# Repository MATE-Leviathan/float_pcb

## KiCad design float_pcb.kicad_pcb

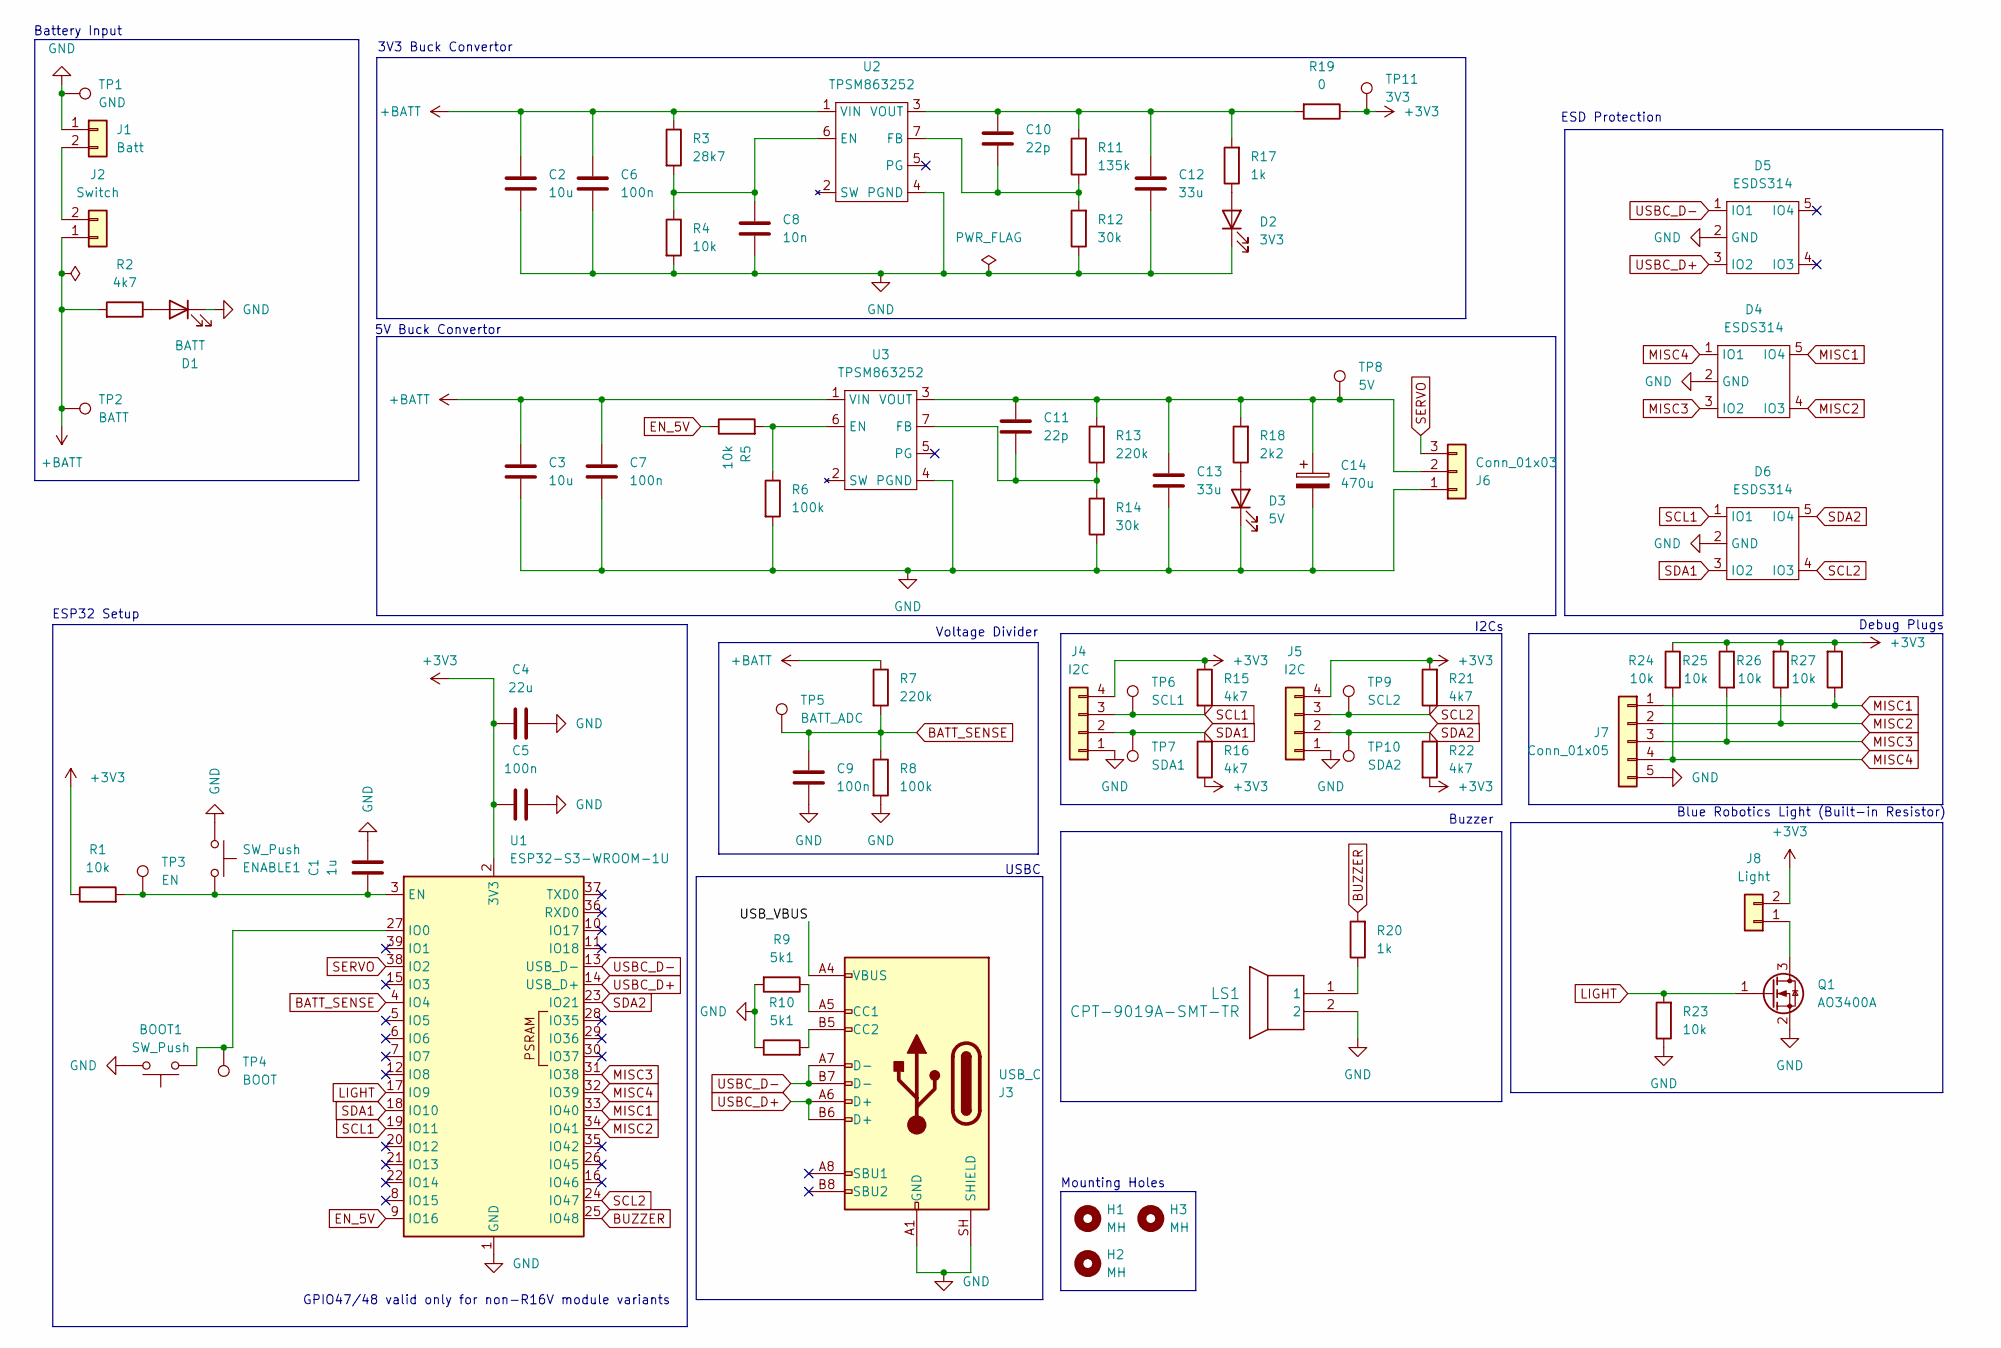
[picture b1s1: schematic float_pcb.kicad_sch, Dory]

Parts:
BOOT1: SW_Push; SW_SPST_TL3342
C1: 1u; C_0603_1608Metric
C2, C3: 10u; C_0805_2012Metric
C4: 22u; C_0603_1608Metric
C5, C6, C7, C9: 100n; C_0603_1608Metric
C8: 10n; C_0603_1608Metric
C10, C11: 22p; C_0603_1608Metric
C12, C13: 33u; C_1206_3216Metric
C14: 470u; CP_Radial_D6.3mm_P2.50mm
D1: BATT; LED_0603_1608Metric
D2: 3V3; LED_0603_1608Metric
D3: 5V; LED_0603_1608Metric
D4, D5, D6: ESDS314; SOT-23-5
ENABLE1: SW_Push; SW_SPST_TL3342
H1, H2, H3: MH; MountingHole_2.2mm_M2
J1: Batt; AMASS_XT30U-M_1x02_P5.0mm_Vertical
J2: Switch; JST_XH_B2B-XH-A_1x02_P2.50mm_Vertical
J3: USB_C; USB_C_Receptacle_GCT_USB4105-xx-A_16P_TopMnt_Horizontal
J4, J5: I2C; JST_XH_B4B-XH-A_1x04_P2.50mm_Vertical
J6: Conn_01x03; JST_XH_B3B-XH-A_1x03_P2.50mm_Vertical
J7: Conn_01x05; PinHeader_1x05_P2.54mm_Vertical
J8: Light; JST_XH_B2B-XH-A_1x02_P2.50mm_Vertical
LS1: CPT-9019A-SMT-TR; CPT-9019A_CUD
Q1: AO3400A; SOT-23
R1, R4, R5, R23, R24, R25, R26, R27: 10k; R_0603_1608Metric
R2, R15, R16, R21, R22: 4k7; R_0603_1608Metric
R3: 28k7; R_0603_1608Metric
R6, R8: 100k; R_0603_1608Metric
R7, R13: 220k; R_0603_1608Metric
R9, R10: 5k1; R_0603_1608Metric
R11: 135k; R_0603_1608Metric
R12, R14: 30k; R_0603_1608Metric
R17, R20: 1k; R_0603_1608Metric
R18: 2k2; R_0603_1608Metric
R19: 0; R_0603_1608Metric
TP1: GND; TestPoint_Pad_D1.5mm
TP2: BATT; TestPoint_Pad_D1.5mm
TP3: EN; TestPoint_Pad_D1.5mm
TP4: BOOT; TestPoint_Pad_D1.5mm
TP5: BATT_ADC; TestPoint_Pad_D1.5mm
TP6: SCL1; TestPoint_Pad_D1.5mm
TP7: SDA1; TestPoint_Pad_D1.5mm
TP8: 5V; TestPoint_Pad_D1.5mm
TP9: SCL2; TestPoint_Pad_D1.5mm
TP10: SDA2; TestPoint_Pad_D1.5mm
TP11: 3V3; TestPoint_Pad_D1.5mm
U1: ESP32-S3-WROOM-1U
U2, U3: TPSM863252; TPSM86325x_RDX0007A

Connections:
+3V3: C4.1, C5.1, J4.4, J5.4, J8.2, R1.1, R15.1, R16.1, R19.1, R21.2, R22.2, R24.1, R25.1, R26.2, R27.2, TP11.1 (1_1), U1.2 (3V3)
+BATT: C2.1, C3.1, C6.2, C7.2, J2.1, R2.2, R3.1, R7.1, TP2.1 (1_1), U2.1 (VIN), U3.1 (VIN)
/USB_VBUS: J3.A4 (VBUS), J3.A9 (VBUS), J3.B4 (VBUS), J3.B9 (VBUS)
BATT_SENSE: C9.1, R7.2, R8.1, TP5.1 (1_1), U1.4 (IO4)
BUZZER: R20.2, U1.25 (IO48)
EN_5V: R5.1, U1.9 (IO16)
GND: BOOT1.2, C1.1, C2.2, C3.2, C4.2, C5.2, C6.1, C7.1, C8.1, C9.2, C12.1, C13.1, C14.2, D1.1 (K), D2.1 (K), D3.1 (K), D4.2 (GND), D5.2 (GND), D6.2 (GND), ENABLE1.1, J1.1, J3.A1 (GND), J3.A12 (GND), J3.B1 (GND), J3.B12 (GND), J3.SH (SHIELD), J4.1, J5.1, J6.1, J7.5, LS1.2, Q1.2 (S), R4.2, R6.2, R8.2, R9.2, R10.1, R12.1, R14.1, R23.1, TP1.1 (1_1), U1.1 (GND), U1.40 (GND), U1.41 (GND), U2.4 (PGND), U3.4 (PGND)
LIGHT: Q1.1 (G), R23.2, U1.17 (IO9)
MISC1: D4.5 (IO4), J7.1, R27.1, U1.33 (IO40)
MISC2: D4.4 (IO3), J7.2, R26.1, U1.34 (IO41)
MISC3: D4.3 (IO2), J7.3, R25.2, U1.31 (IO38)
MISC4: D4.1 (IO1), J7.4, R24.2, U1.32 (IO39)
unnamed: D1.2 (A), R2.1
unnamed: D2.2 (A), R17.1
unnamed: D3.2 (A), R18.1
unnamed: J1.2, J2.2
unnamed: J3.A5 (CC1), R9.1
unnamed: J3.B5 (CC2), R10.2
unnamed: C11.1, C13.2, C14.1, J6.2, R13.2, R18.2, TP8.1 (1_1), U3.3 (VOUT)
unnamed: J8.1, Q1.3 (D)
unnamed: LS1.1, R20.1
unnamed: C1.2, ENABLE1.2, R1.2, TP3.1 (1_1), U1.3 (EN)
unnamed: BOOT1.1, TP4.1 (1_1), U1.27 (IO0)
unnamed: C8.2, R3.2, R4.1, U2.6 (EN)
unnamed: C10.2, R11.1, R12.2, U2.7 (FB)
unnamed: C10.1, C12.2, R11.2, R17.2, R19.2, U2.3 (VOUT)
unnamed: R5.2, R6.1, U3.6 (EN)
unnamed: C11.2, R13.1, R14.2, U3.7 (FB)
SCL1: D6.1 (IO1), J4.3, R15.2, TP6.1 (1_1), U1.19 (IO11)
SCL2: D6.4 (IO3), J5.3, R21.1, TP9.1 (1_1), U1.24 (IO47)
SDA1: D6.3 (IO2), J4.2, R16.2, TP7.1 (1_1), U1.18 (IO10)
SDA2: D6.5 (IO4), J5.2, R22.1, TP10.1 (1_1), U1.23 (IO21)
SERVO: J6.3, U1.38 (IO2)
USBC_D+: D5.3 (IO2), J3.A6 (D+), J3.B6 (D+), U1.14 (USB_D+)
USBC_D-: D5.1 (IO1), J3.A7 (D-), J3.B7 (D-), U1.13 (USB_D-)

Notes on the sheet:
Mounting Holes
ESP32 Setup
I2Cs
ESD Protection
Battery Input
USBC
3V3 Buck Convertor
Blue Robotics Light (Built-in Resistor)
5V Buck Convertor
GPIO47/48 valid only for non-R16V module variants
Buzzer
Voltage Divider
Debug Plugs

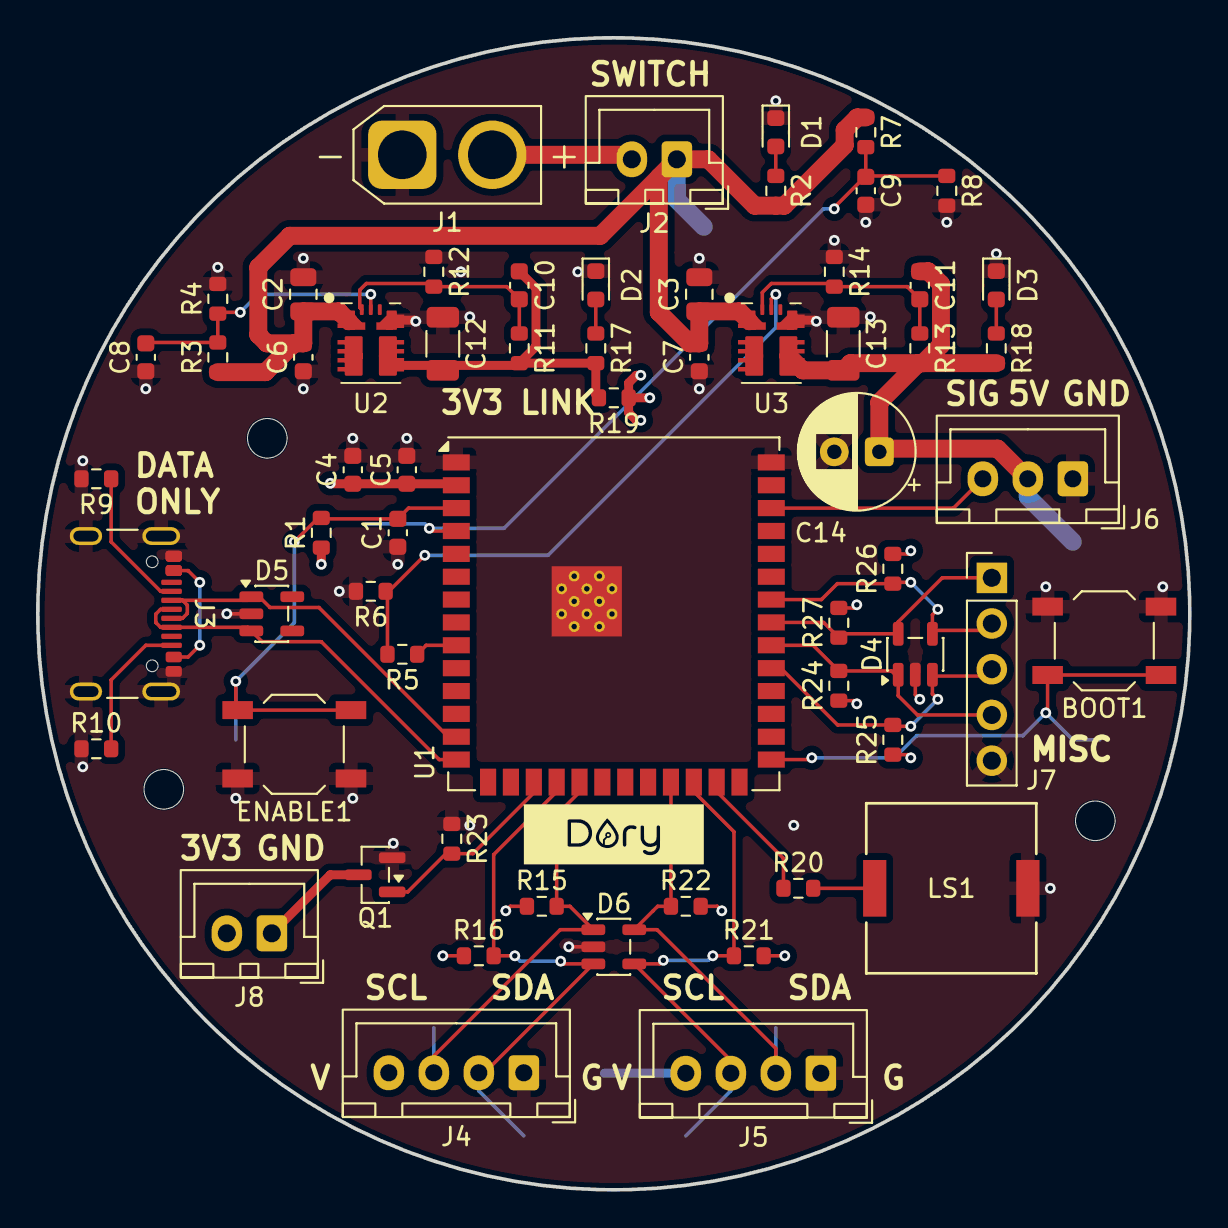
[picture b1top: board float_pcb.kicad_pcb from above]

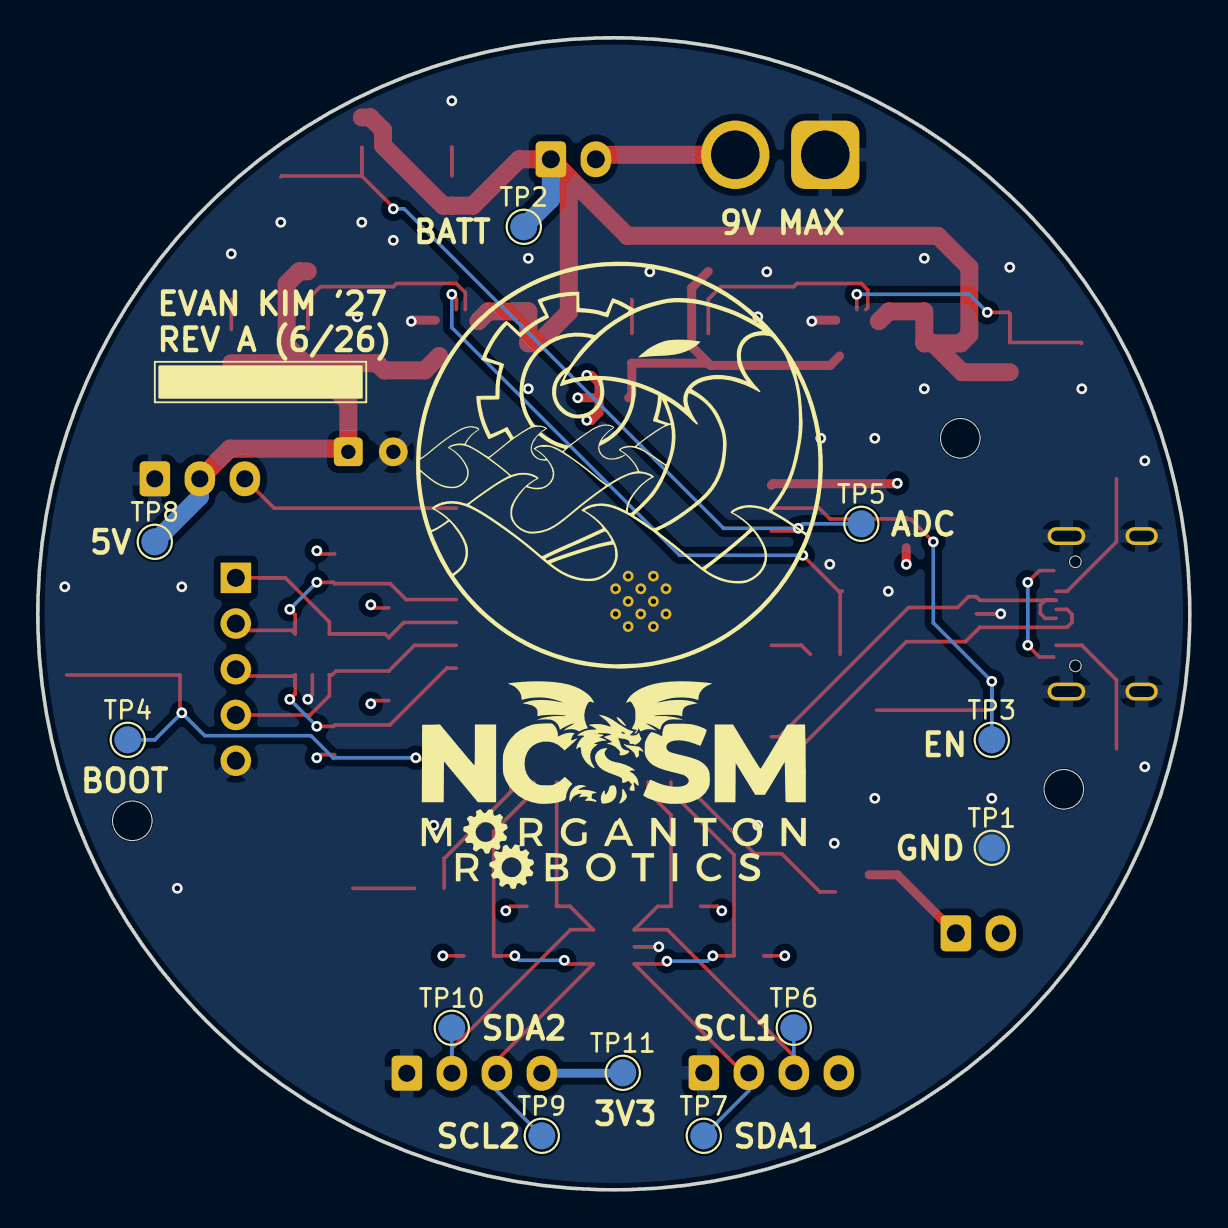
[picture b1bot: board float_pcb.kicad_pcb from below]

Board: 4 copper layers, 64.0 x 64.0 mm, 76 parts (11 on the bottom side), 35 nets.

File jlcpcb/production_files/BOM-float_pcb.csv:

Comment,Designator,Footprint,LCSC,Quantity
Conn_01x03,J6,JST_XH_B3B-XH-A_1x03_P2.50mm_Vertical,,1
Batt,J1,AMASS_XT30U-M_1x02_P5.0mm_Vertical,,1
470u,C14,CP_Radial_D6.3mm_P2.50mm,,1
100n,C7,C_0603_1608Metric,,1
100k,R6,R_0603_1608Metric,,1
AO3400A,Q1,SOT-23,,1
22u,C4,C_0603_1608Metric,,1
5V,D3,LED_0603_1608Metric,,1
4k7,R16,R_0603_1608Metric,,1
10u,C2,C_0805_2012Metric,,1
135k,R11,R_0603_1608Metric,,1
10u,C3,C_0805_2012Metric,,1
220k,R7,R_0603_1608Metric,,1
100n,C5,C_0603_1608Metric,,1
TPSM863252,U2,TPSM86325x_RDX0007A,,1
33u,C13,C_1206_3216Metric,,1
33u,C12,C_1206_3216Metric,,1
28k7,R3,R_0603_1608Metric,,1
100k,R8,R_0603_1608Metric,,1
SW_Push,BOOT1,SW_SPST_TL3342,,1
100n,C6,C_0603_1608Metric,,1
30k,R12,R_0603_1608Metric,,1
220k,R13,R_0603_1608Metric,,1
4k7,R2,R_0603_1608Metric,,1
Conn_01x05,J7,PinHeader_1x05_P2.54mm_Vertical,,1
22p,C10,C_0603_1608Metric,,1
30k,R14,R_0603_1608Metric,,1
10k,R4,R_0603_1608Metric,,1
1u,C1,C_0603_1608Metric,,1
10k,R1,R_0603_1608Metric,,1
USB_C,J3,USB_C_Receptacle_GCT_USB4105-xx-A_16P_TopMnt_Horizontal,,1
5k1,R9,R_0603_1608Metric,,1
4k7,R15,R_0603_1608Metric,,1
3V3,D2,LED_0603_1608Metric,,1
ESP32-S3-WROOM-1U,U1,ESP32-S3-WROOM-1U,,1
10n,C8,C_0603_1608Metric,,1
I2C,J5,JST_XH_B4B-XH-A_1x04_P2.50mm_Vertical,,1
5k1,R10,R_0603_1608Metric,,1
10k,R5,R_0603_1608Metric,,1
100n,C9,C_0603_1608Metric,,1
BATT,D1,LED_0603_1608Metric,,1
SW_Push,ENABLE1,SW_SPST_TL3342,,1
1k,R17,R_0603_1608Metric,,1
0,R19,R_0603_1608Metric,,1
2k2,R18,R_0603_1608Metric,,1
1k,R20,R_0603_1608Metric,,1
CPT-9019A-SMT-TR,LS1,CPT-9019A_CUD,,1
I2C,J4,JST_XH_B4B-XH-A_1x04_P2.50mm_Vertical,,1
Switch,J2,JST_XH_B2B-XH-A_1x02_P2.50mm_Vertical,,1
BOOT,TP4,TestPoint_Pad_D1.5mm,,1
EN,TP3,TestPoint_Pad_D1.5mm,,1
BATT,TP2,TestPoint_Pad_D1.5mm,,1
GND,TP1,TestPoint_Pad_D1.5mm,,1
TPSM863252,U3,TPSM86325x_RDX0007A,,1
10k,R26,R_0603_1608Metric,,1
10k,R25,R_0603_1608Metric,,1
10k,R24,R_0603_1608Metric,,1
10k,R23,R_0603_1608Metric,,1
4k7,R22,R_0603_1608Metric,,1
4k7,R21,R_0603_1608Metric,,1
SDA2,TP10,TestPoint_Pad_D1.5mm,,1
SCL1,TP6,TestPoint_Pad_D1.5mm,,1
SCL2,TP9,TestPoint_Pad_D1.5mm,,1
BATT_ADC,TP5,TestPoint_Pad_D1.5mm,,1
SDA1,TP7,TestPoint_Pad_D1.5mm,,1
5V,TP8,TestPoint_Pad_D1.5mm,,1
ESDS314,D6,SOT-23-5,,1
ESDS314,D4,SOT-23-5,,1
10k,R27,R_0603_1608Metric,,1
22p,C11,C_0603_1608Metric,,1
Light,J8,JST_XH_B2B-XH-A_1x02_P2.50mm_Vertical,,1
ESDS314,D5,SOT-23-5,,1
3V3,TP11,TestPoint_Pad_D1.5mm,,1

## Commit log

2026-05-23 First Version
2026-05-23 Add Image
2026-06-01 Version 3
    Before the big 4 layer migration
2026-06-02 Start of the great multilayer migration
2026-06-03 More progress on V4
2026-06-03 Using open source fonts
2026-06-04 Change hole placement
2026-06-05 Starting V5: new 33uf new servo cap, ADC and voltage dividor
2026-06-05 Continuing Test Pads and some placement things
2026-06-06 V5: Sent for production!
2026-06-06 V5: oopsie with extra via
2026-06-06 Added images of all of the iterations
